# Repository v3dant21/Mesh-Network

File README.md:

# Secure Relay Node Project

This project implements a multi-node end-to-end encrypted (E2EE) real-time mesh messaging layer.

## Architecture Overview

The system consists of two types of nodes:
1. **Intelligent Relay**: A central TCP server that maintains a routing table of connected nodes. It securely routes packets based on their destination ID without being able to decrypt their contents.
2. **Mesh Nodes**: Client nodes that connect to the relay. They generate an ID, broadcast their public key to discover peers, and dynamically negotiate independent end-to-end encrypted sessions with every other node on the network.

## Encryption Flow

- The cryptographic implementation uses `x25519-dalek` for Diffie-Hellman key exchange and `aes-gcm` (AES-256-GCM) for authenticated symmetric encryption.
- When a Node starts, it generates a `StaticSecret` private/public keypair. It broadcasts its public key (`to: 0`) to the Relay, which forwards it to all connected Nodes in a `Handshake` packet.
- Upon receiving a broadcasted public key, other Nodes generate a shared secret for that specific peer, store it in their session list (`HashMap<u32, SessionCrypto>`), and reply with their own public key directly to the sender.
- Every text message is encrypted with a newly generated, randomized 12-byte nonce, which is prepended to the ciphertext before transmission.

## Reliability Mechanisms

- **Structured Packets**: Communication is encapsulated in a `Packet` struct, serialized using `bincode`. It includes `message_id`, `timestamp`, `sender_id`, and `payload_type`.
- **Deduplication**: Nodes track `message_id` to ignore duplicate packets.
- **Acknowledgements & Retries**: Sending a `TextChat` or `Ping` payload enqueues it in a retry pool. Upon receiving an `Ack` payload matching the `message_id`, it is removed. A background task retries unacknowledged messages every few seconds.

## How to Run

### Option 1: Automatic Multi-Node Launch (Recommended)
This will automatically launch the Relay and 3 Nodes (IDs 101, 102, 103) in separate windows using your native terminal emulator (Ghostty, Kitty, GNOME Terminal, CMD, etc).

```bash
cargo run -- all
```

### Option 2: Manual Launch
You can manually start the network across multiple terminal instances.

1. **Start the Relay Node**
   ```bash
   cargo run -- relay
   ```
2. **Start a Mesh Node (Target IP 127.0.0.1, Auto-generate ID)**
   ```bash
   cargo run -- node 127.0.0.1
   ```
3. **Start a Mesh Node (Specific ID)**
   ```bash
   cargo run -- node 127.0.0.1 500
   ```

## Example Chat Session

Once multiple nodes are running, use the interactive terminal commands to chat:
- `/peers`: View a list of all Node IDs you have currently established an encrypted session with.
- `/msg <id> <message>`: Send a direct end-to-end encrypted message to a specific Node ID.
- `/broadcast <message>`: Encrypt and send a message to all connected peers simultaneously.

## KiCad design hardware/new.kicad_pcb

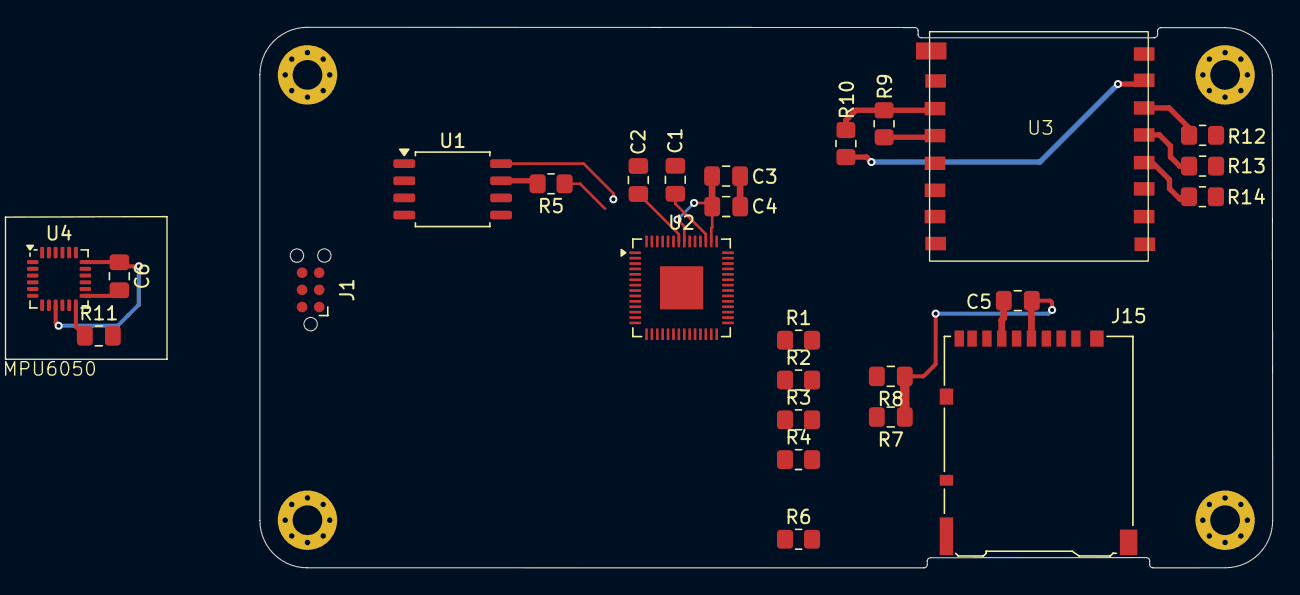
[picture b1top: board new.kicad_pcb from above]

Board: 2 copper layers, 75.1 x 40.1 mm, 26 parts (0 on the bottom side), 40 nets.

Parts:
C1, C4: 1micro; C_0805_2012Metric_Pad1.18x1.45mm_HandSolder
C2: 1 nano; C_0805_2012Metric_Pad1.18x1.45mm_HandSolder
C3, C5, C6: 100nf; C_0805_2012Metric_Pad1.18x1.45mm_HandSolder
J1: Conn_ARM_SWD_TagConnect_TC2030-NL; Tag-Connect_TC2030-IDC-NL_2x03_P1.27mm_Vertical
J15: Micro_SD_Card_Det1; microSD_HC_Hirose_DM3AT-SF-PEJM5
R1, R2, R3, R4, R5, R12, R13, R14: 22; R_0805_2012Metric_Pad1.20x1.40mm_HandSolder
R6, R9, R10: 10k; R_0805_2012Metric_Pad1.20x1.40mm_HandSolder
R7, R8: 10k; C_0805_2012Metric_Pad1.18x1.45mm_HandSolder
R11: 22; C_0805_2012Metric_Pad1.18x1.45mm_HandSolder
U1: W25Q128JVS; SOIC-8_5.3x5.3mm_P1.27mm
U2: RP2040; QFN-56-1EP_7x7mm_P0.4mm_EP3.2x3.2mm
U3: SX1262B
U4: MPU-6050; InvenSense_QFN-24_4x4mm_P0.5mm

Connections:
+3.3V: C3.1, C4.1, C5.1, J15.4 (VDD), R6.1, R7.1, R8.1, R9.1, R10.1, U1.8 (VCC), U2.1 (IOVDD), U2.10 (IOVDD), U2.22 (IOVDD), U2.33 (IOVDD), U2.42 (IOVDD), U2.44 (VREG_IN), U2.49 (IOVDD), U3.3 (3.3v)
FLASH.CLK: R1.1, U2.52 (QSPI_SCLK)
FLASH.CS#: R6.2, U1.1 (~CS), U2.56 (QSPI_SS)
FLASH.DI (IO0): R2.2, U2.53 (QSPI_SD0)
FLASH.DO (IO1): R3.2, U2.55 (QSPI_SD1)
GND: C5.2, C6.1, J1.5 (GND), J15.6 (VSS), J15.10 (SHIELD), U1.4 (GND), U2.57 (GND), U3.2 (GND), U3.9 (GND), U3.16 (GND), U4.9 (AD0), U4.18 (GND)
IO2/WP#: R4.1, U2.54 (QSPI_SD2)
IO3/HOLD#/RESET#: R5.1, U2.51 (QSPI_SD3)
J2.CLK: J15.5 (CLK), U2.7 (GPIO5)
J2.CMD: J15.3 (CMD), R7.2, U2.6 (GPIO4)
J2.DAT0: J15.7 (DAT0), R8.2, U2.8 (GPIO6)
J2.DAT3/CD: J15.2 (DAT3/CD), U2.9 (GPIO7)
J2.DET: J15.9 (DET), U2.32 (GPIO21)
MPU6050.INT: R11.1, U2.16 (GPIO13), U4.12 (INT)
MPU6050.SCL: U2.12 (GPIO9), U4.23 (SCL)
MPU6050.SDA: U2.11 (GPIO8), U4.24 (SDA)
unnamed: C1.2, C2.2, C3.2, C4.2
unnamed: C2.1, U2.23 (DVDD), U2.50 (DVDD)
unnamed: R1.2, U1.6 (CLK)
unnamed: R2.1, U1.5 (DI/IO_{0})
unnamed: R3.1, U1.2 (DO/IO_{1})
unnamed: R5.2, U1.7 (~HOLD/~RESET/IO_{3})
unnamed: R4.2, U1.3 (~WP/IO_{2})
unnamed: C1.1, U2.45 (VREG_VOUT)
unnamed: R13.1, U3.13 (MISO)
unnamed: R12.1, U3.14 (MOSI)
unnamed: R14.1, U3.12 (SCK)
unnamed: C6.2, U4.13 (VDD)
R.GPIO10: U2.13 (GPIO10), U3.6 (DIO1)
R.GPIO11: U2.14 (GPIO11), U3.7 (DIO2)
R.GPIO12: U2.15 (GPIO12), U3.10 (BUSY)
R.GPIO16: R13.2, U2.27 (GPIO16)
R.GPIO17: R10.2, U2.28 (GPIO17), U3.15 (NSS)
R.GPIO18: R14.2, U2.29 (GPIO18)
R.GPIO19: R12.2, U2.30 (GPIO19)
R.GPIO24: U2.36 (GPIO24), U3.8 (DIO3)
R.GPIO25: R9.2, U2.37 (GPIO25), U3.4 (RST)
R.RUN: J1.3 (~RESET), U2.26 (RUN)
R.SWCLK: J1.4 (SWCLK), U2.24 (SWCLK)
R.SWD: J1.2 (SWDIO), U2.25 (SWD)

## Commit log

2025-12-01 initial
2025-12-02 cli tool
2025-12-07 added harware and PCB schematics
2026-05-07 chat terminal edition
2026-05-11 encryption added
2026-05-13 dead inside
2026-06-23 Update mesh network project
